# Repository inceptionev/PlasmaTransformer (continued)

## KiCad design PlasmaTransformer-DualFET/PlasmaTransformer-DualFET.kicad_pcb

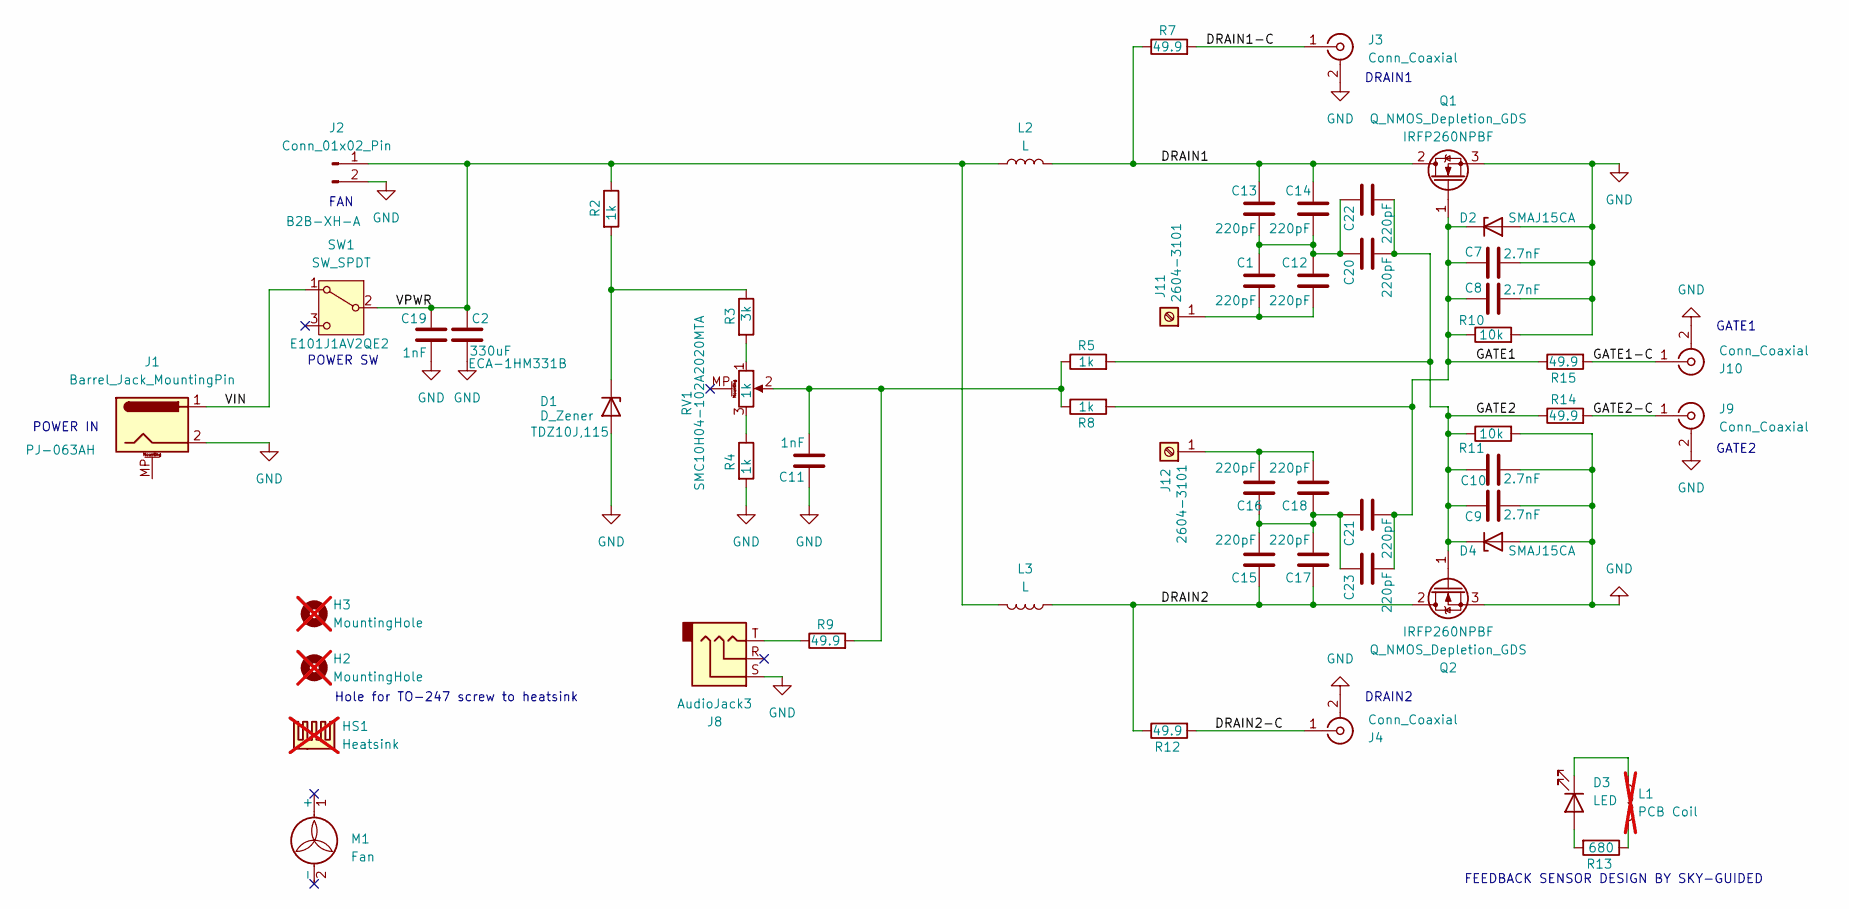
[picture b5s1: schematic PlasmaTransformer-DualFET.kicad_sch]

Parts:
C1, C12, C13, C14, C15, C16, C17, C18, C20, C21, C22, C23: 220pF; C_Disc_D10.5mm_W5.0mm_P10.00mm
C2: 330uF; CP_Radial_D10.0mm_P5.00mm; MPN ECA-1HM331B
C7, C8, C9, C10: 2.7nF; C_1812_4532Metric; MPN 1812GC272KAT1A
C11, C19: 1nF; C_1812_4532Metric; MPN VJ1812A102JXFTW1HV
D1: D_Zener; D_SOD-323_HandSoldering; MPN TDZ10J,115
D2, D4: SMAJ15CA; D_SMC; MPN SMCJ15A
D3: LED; LED_1206_3216Metric; MPN 150120AS75000
H2, H3: MountingHole; MountingHole_8.4mm_M8; not fitted
HS1: Heatsink; Heatsink_75x37.5mm_Fischer_SK-594-37.5-AL; not fitted
J1: Barrel_Jack_MountingPin; BarrelJack_CUI_PJ-063AH_Horizontal; MPN PJ-063AH
J2: Conn_01x02_Pin; JST_XH_B2B-XH-AM_1x02_P2.50mm_Vertical; MPN B2B-XH-A
J3, J4, J9, J10: Conn_Coaxial; SMA_Amphenol_901-144_Vertical; MPN RFPC-SMA27-F
J8: AudioJack3; Jack_3.5mm_CUI_SJ-3523-SMT_Horizontal; MPN SJ-3523-SMT-TR
J11, J12: Screw_Terminal_01x01; CONN_2604-3101_WAG; MPN 2604-3101
L1: PCB Coil; FEEDBACK_COIL_B; not fitted
L2, L3: L; L_APV_APH1770; MPN SRP1265C-6R8M
M1: Fan; FAN AXIAL 92X25.4MM; MPN AFB0924VH-R00
Q1, Q2: Q_NMOS_Depletion_GDS; TO-247-3_Horizontal_TabDown; MPN IRFP260NPBF
R2, R4, R5, R8: 1k; R_0805_2012Metric; MPN RC0805FR-071KL
R3: 3k; R_0805_2012Metric; MPN RC0805FR-073KL
R7, R9, R12, R14, R15: 49.9; R_0805_2012Metric; MPN RC0805FR-0749R9L
R10, R11: 10k; R_0805_2012Metric; MPN RC0805FR-071KL
R13: 680; R_0805_2012Metric; MPN RC0805FR-07680RL
RV1: 1k; SMC10H04-102A2020MTA; MPN SMC10H04-102A2020MTA
SW1: SW_SPDT; CKSW-E101J1AV2QE2; MPN E101J1AV2QE2

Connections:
/DRAIN1: C13.1, C14.1, L2.2, Q1.2 (D), R7.1
/DRAIN1-C: J3.1 (In), R7.2
/DRAIN2: C15.1, C17.1, L3.1, Q2.2 (D), R12.1
/DRAIN2-C: J4.1 (In), R12.2
/GATE1: C7.1, C8.1, C21.2, C23.2, D2.1 (K), Q1.1 (G), R8.2, R10.1, R15.1
/GATE1-C: J10.1 (In), R15.2
/GATE2: C9.1, C10.1, C20.2, C22.2, D4.1 (K), Q2.1 (G), R5.2, R11.1, R14.1
/GATE2-C: J9.1 (In), R14.2
/VIN: J1.1, SW1.1 (A)
/VPWR: C2.1, C19.2, J2.1, L2.1, L3.2, R2.1, SW1.2 (B)
GND: C2.2, C7.2, C8.2, C9.2, C10.2, C11.1, C19.1, D1.2 (A), D2.2 (A), D4.2 (A), J1.2, J2.2, J3.2 (Ext), J4.2 (Ext), J8.S, J9.2 (Ext), J10.2 (Ext), Q1.3 (S), Q2.3 (S), R4.2, R10.2, R11.2
unnamed: C1.1, C12.1, C13.2, C14.2, C20.1, C22.1
unnamed: C11.2, R5.1, R8.1, R9.2, RV1.2
unnamed: C15.2, C16.1, C17.2, C18.1, C21.1, C23.1
unnamed: D1.1 (K), R2.2, R3.1
unnamed: D3.2 (A), R13.2
unnamed: D3.1 (K), L1.1
unnamed: J8.T, R9.1
unnamed: C1.2, C12.2, J11.1
unnamed: C16.2, C18.2, J12.1
unnamed: L1.2, R13.1
unnamed: R3.2, RV1.1
unnamed: R4.1, RV1.3

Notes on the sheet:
DRAIN2
Hole for TO-247 screw to heatsink
FEEDBACK SENSOR DESIGN BY SKY-GUIDED
GATE1
POWER IN
DRAIN1
POWER SW
GATE2
FAN

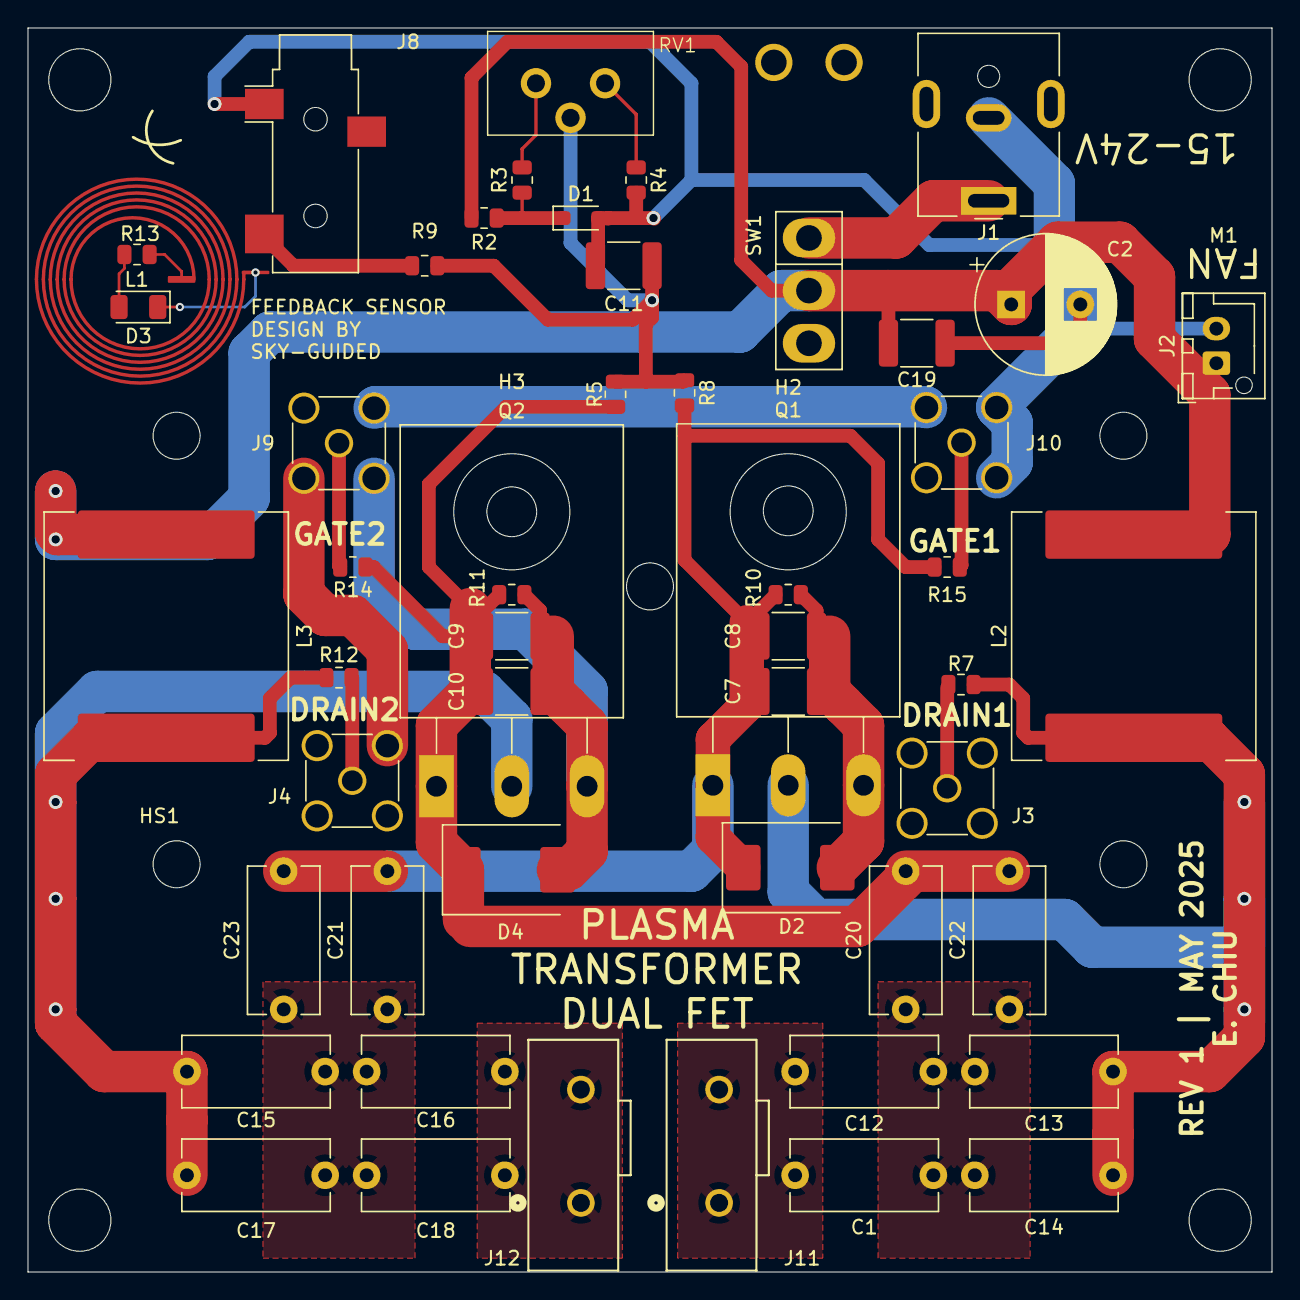
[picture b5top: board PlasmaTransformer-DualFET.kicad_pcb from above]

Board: 2 copper layers, 90.0 x 90.0 mm, 56 parts (0 on the bottom side), 23 nets.

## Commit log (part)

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2025-04-30 placement complete, commit before routing
2025-04-30 layout complete, commit before resync
2025-04-30 final edits, silkscreens, generate Rev 1 manufacturing files
2025-05-20 adding BOM files and 3D design for coil support and fan shroud for 130cm globe
2025-05-20 updated 122mm coil form design
2025-05-20 added foot for airflow
2025-05-27 Updated rev 2 design and manufacturing files. Note BOM is not up to date.
2025-05-27 added design for 20cm globe
2025-06-07 adding corrugated shroud design, BOM for dual fet driver
2025-06-12 updated 20cm corrugated shroud design
2025-06-12 Added foot
2025-06-20 added coil form and new version of shroud with notch for fan wires
2025-06-23 modifying recommended values for successful 20cm toroid halo
2025-06-23 added front shield to spacer to prevent people touching the coil, and recessed the coil down also to make it more difficult to accidentally touch the coil. Removed lower cooling holes as they don't r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
2025-06-23 reorganized stls into folders to make them easier to find
2025-06-23 adding images for readme
2025-06-23 adding readme
2025-06-23 Update README.md
    fixing errors
2025-06-23 Update README.md
    updated formatting
2025-06-23 Update README.md
    clarifications
2025-06-25 Update README.md
    added assembly instructions and additional materials
2025-06-25 Update README.md
    added step to tighten mosfet screw
2025-06-27 rev 3 PCB adds auto ignite
2025-06-28 Design cleanup, part selection and BOM update
2025-06-28 adding design and manufacturing files, not BOM is not yet complete
2025-06-28 part selection and bom
2025-06-28 graphical fixes to BOM
2025-07-01 added feet mounting holes to 13cm shroud
2025-07-08 Updating to new design with snap-in front cover
2025-07-08 adding 3d print files with new design with cover
2025-07-08 reorganizing PCB files into folders
2025-07-08 rename folder
2025-07-08 Update README.md
    updated instructions for design using 4mm bowden tube insulation, updated file location callouts
2025-07-08 update links in assembly
2025-07-11 adding rev 3B with RF node igniter design
2025-07-11 fixced clearances and generated gerbers
2025-07-11 Update README.md
    fixed bowden tube lengths
2025-07-17 added a mount for a 42x24x16mm common mode ferrite to protect the power supply.
2025-07-19 added fan connector assembly assist notch
2025-07-24 adding PDF schematic
2025-07-25 Update README.md
    added credit to Sky-guided and ltwin8, changed capacitance recommendation for 20cm globe
2025-07-27 adding drok supply case to 3d print
2025-07-27 typos, additional details
2025-07-29 layout updates for Rev 3B > Rev 4: gate selector caps, SMD footprint for trigger coil, silkscreen updates
2025-07-30 13cm V2 design WIP, updates to Rev 4 PCB
2025-07-31 create updated 13cm design with coil spacer and cover
2025-07-31 Rolling auto igniter Rev 4 into the main folder
2025-07-31 moving deprecated versions. RF tap auto igniter design rolled into main rev 4
2025-07-31 Rev 4 publish, silkscreen fixes, adding 3d models and footprint library.
2025-07-31 Update README.md
    updates for Rev 4 PCB
2025-07-31 adding image of rev 4 PCB
2025-08-02 adding wireless power necklace
2025-08-11 adding ConformalCoatingJig and 80mm-CoilForm
2025-09-23 Update README.md
    adding coil and insulation lengths for 4-coil 13cm globe
2025-09-24 WIP rev 5
2025-09-24 WIP layout
2025-10-03 library updates
2025-10-05 convert tank caps to push fit sockets
2025-10-10 update library
2025-10-10 WIP rev 5 rebase
2025-10-10 improvements to ease of assembly, increased use of solid pours, layout complete, 1st DRC check complete.
2025-10-11 clean up for manufacturing
2025-10-12 Clean up, silkscreens, BOM cleanup, title blocks, fab notes, generate manufacturing files
2025-10-12 Update README.md
    updates for Rev 5 and adding tips and tricks
2025-10-12 updating 3D print files for 13cm globe rev 5
2025-10-12 adding schematic PDF rev 5
2025-10-14 Update README.md
    improvements to instructions
2025-10-30 WIP rev
2025-10-30 mounting holes and silkscreens
2025-10-30 adding missing 3d print files to 13cm set
2025-10-30 adding coil form for 6mm insulator 13cm Globe coil
2025-10-30 Update README.md
    added measured inductance for coils
2025-11-06 Update README.md
    Added Rev 5 assembly note about socket holes too big for press fit
2025-11-07 Update README.md corrected BOM reference
2025-11-07 Update 13cm tank cap
2025-11-24 cleanup
2025-11-29 layout of feedback circuit
2025-11-29 routing complete, DRC check OK
2025-11-29 add QR code for docs to backside silkscreen
2025-11-29 update silkscreens
2025-11-30 generate manufacturing files
2025-12-03 fab fixes, soldermask defined pad for SOT-23-8
2025-12-16 adding 3d coil form parts
2025-12-16 adding reference desigators to list of components to DNP from turnkey assembly
2026-02-04 adding quad supply
